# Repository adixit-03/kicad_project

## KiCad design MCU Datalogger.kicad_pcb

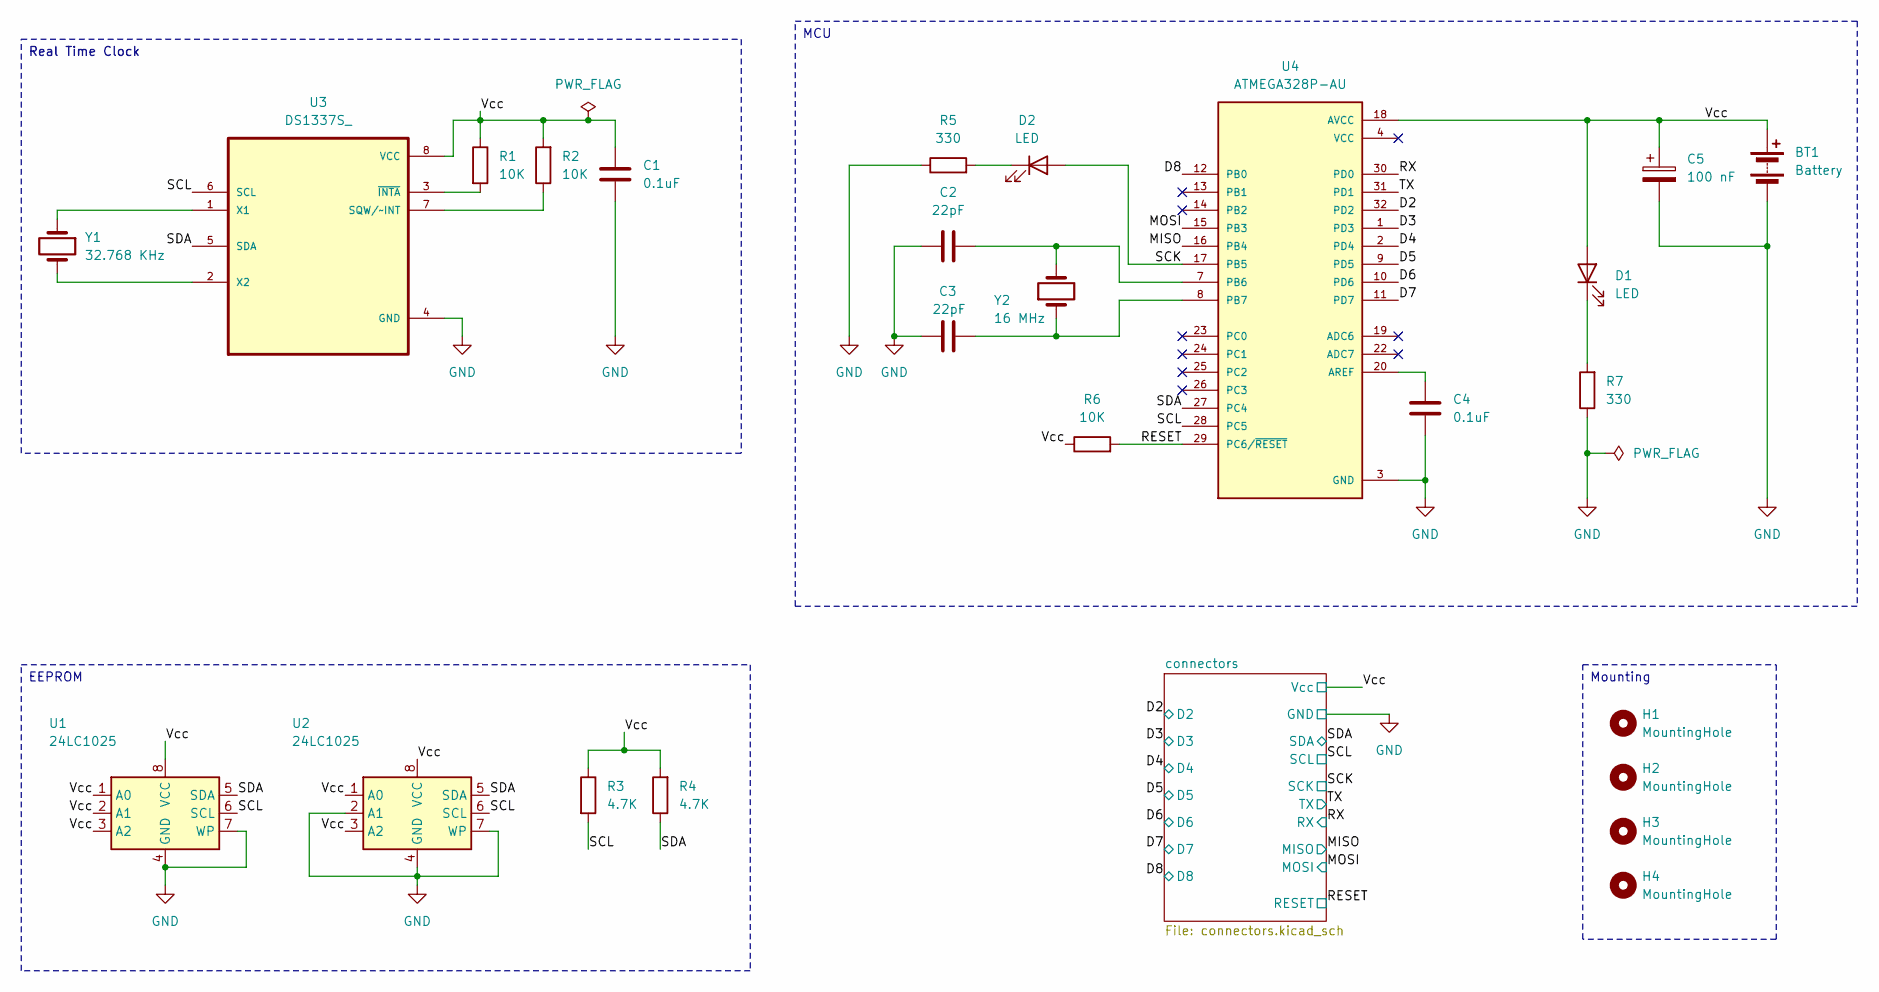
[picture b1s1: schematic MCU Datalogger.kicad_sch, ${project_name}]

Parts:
BT1: Battery; PinHeader_1x02_P2.54mm_Vertical
C1, C4: 0.1uF; C_0805_2012Metric
C2, C3: 22pF; C_0805_2012Metric
C5: 100 nF; C_0805_2012Metric
D1, D2: LED; LED_0805_2012Metric
H1, H2, H3, H4: MountingHole; MountingHole_2.1mm
R1, R2, R6: 10K; R_0805_2012Metric
R3, R4: 4.7K; R_0805_2012Metric
R5, R7: 330; R_0805_2012Metric
U1, U2: 24LC1025; SOIC-8_5.3x5.3mm_P1.27mm
U3: DS1337S_; SOIC127P600X175-8N
U4: ATMEGA328P-AU; QFP80P900X900X120-32N; PARTREV 8271A
Y1: 32.768 KHz; Crystal_SMD_5032-2Pin_5.0x3.2mm_HandSoldering
Y2: 16 MHz; Crystal_SMD_5032-2Pin_5.0x3.2mm_HandSoldering

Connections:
/D2: U4.32 (PD2); also elsewhere on the board
/D3: U4.1 (PD3); also elsewhere on the board
/D4: U4.2 (PD4); also elsewhere on the board
/D5: U4.9 (PD5); also elsewhere on the board
/D6: U4.10 (PD6); also elsewhere on the board
/D7: U4.11 (PD7); also elsewhere on the board
/D8: U4.12 (PB0); also elsewhere on the board
/MISO: U4.16 (PB4); also elsewhere on the board
/MOSI: U4.15 (PB3); also elsewhere on the board
/RESET: R6.2, U4.29 (PC6/~RESET); also elsewhere on the board
/RX: U4.30 (PD0); also elsewhere on the board
/SCK: D2.2 (A), U4.17 (PB5); also elsewhere on the board
/SCL: R3.2, U1.6 (SCL), U2.6 (SCL), U3.6 (SCL), U4.28 (PC5); also elsewhere on the board
/SDA: R4.1, U1.5 (SDA), U2.5 (SDA), U3.5 (SDA), U4.27 (PC4); also elsewhere on the board
/TX: U4.31 (PD1); also elsewhere on the board
/Vcc: BT1.1 (+), C1.2, C5.1, D1.2 (A), R1.1, R2.2, R3.1, R4.2, R6.1, U1.1 (A0), U1.2 (A1), U1.3 (A2), U1.8 (VCC), U2.1 (A0), U2.3 (A2), U2.8 (VCC), U3.8 (VCC), U4.18 (AVCC); also elsewhere on the board
GND: BT1.2 (-), C1.1, C2.1, C3.1, C4.1, C5.2, R5.1, R7.1, U1.4 (GND), U1.7 (WP), U2.2 (A1), U2.4 (GND), U2.7 (WP), U3.4 (GND), U4.3 (GND), U4.5 (GND), U4.21 (GND); also elsewhere on the board
unnamed: D1.1 (K), R7.2
unnamed: D2.1 (K), R5.2
unnamed: R2.1, U3.7 (SQW/~INT)
unnamed: U3.1 (X1), Y1.1
unnamed: U3.2 (X2), Y1.2
unnamed: R1.2, U3.3 (~INTA)
unnamed: C4.2, U4.20 (AREF)
unnamed: C2.2, U4.7 (PB6), Y2.2
unnamed: C3.2, U4.8 (PB7), Y2.1
VCC: U4.4 (VCC), U4.6 (VCC)

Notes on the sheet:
Mounting
Real Time Clock
MCU
EEPROM

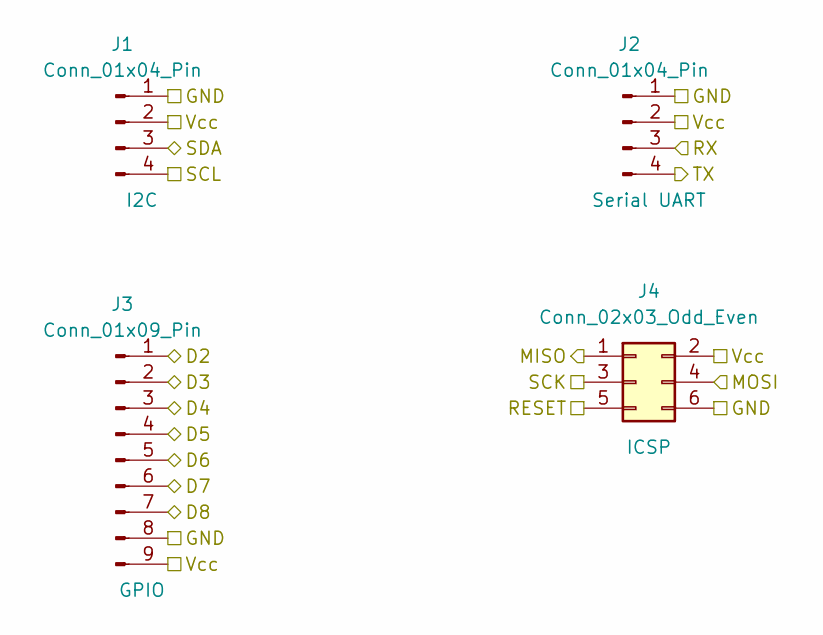
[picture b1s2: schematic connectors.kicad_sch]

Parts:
J1, J2: Conn_01x04_Pin; PinHeader_1x04_P2.54mm_Vertical
J3: Conn_01x09_Pin; PinHeader_1x09_P2.54mm_Vertical
J4: Conn_02x03_Odd_Even; PinHeader_2x03_P2.54mm_Vertical

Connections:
/D2: J3.1; also elsewhere on the board
/D3: J3.2; also elsewhere on the board
/D4: J3.3; also elsewhere on the board
/D5: J3.4; also elsewhere on the board
/D6: J3.5; also elsewhere on the board
/D7: J3.6; also elsewhere on the board
/D8: J3.7; also elsewhere on the board
/MISO: J4.1; also elsewhere on the board
/MOSI: J4.4; also elsewhere on the board
/RESET: J4.5; also elsewhere on the board
/RX: J2.3; also elsewhere on the board
/SCK: J4.3; also elsewhere on the board
/SCL: J1.4; also elsewhere on the board
/SDA: J1.3; also elsewhere on the board
/TX: J2.4; also elsewhere on the board
/Vcc: J1.2, J2.2, J3.9, J4.2; also elsewhere on the board
GND: J1.1, J2.1, J3.8, J4.6; also elsewhere on the board

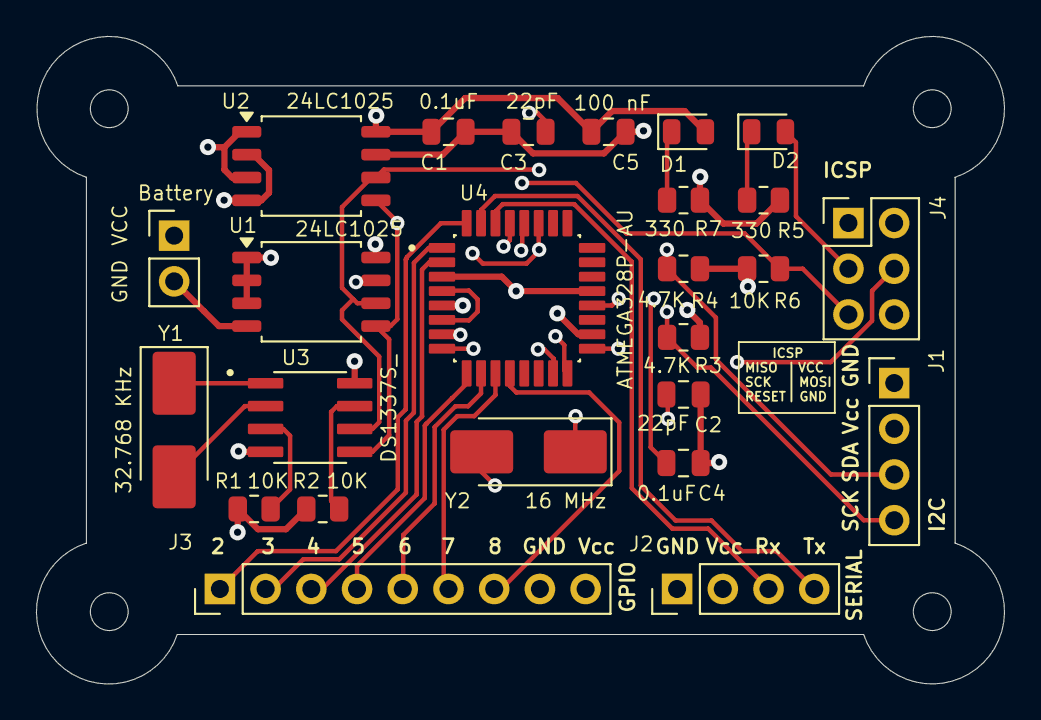
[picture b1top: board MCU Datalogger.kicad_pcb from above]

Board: 4 copper layers, 53.8 x 36.0 mm, 29 parts (0 on the bottom side), 27 nets.

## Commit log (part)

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2026-06-19 Setup of EEschema for new project.
2026-06-23 Have added required symbols to the schematic sheets.
2026-06-24 Changed locations of symbols (arrange).
2026-06-24 Added component values.
2026-06-24 Completed symbol-footprint associations.
2026-06-24 Completed wiring on main sheet.
2026-06-24 Completed wiring in the second sheet.
2026-06-26 Allocated GND and Vcc nets to power net class.
2026-06-26 Completed comments.
2026-06-26 Update MCU Datalogger project
2026-06-27 Setup Pcbnew.
2026-06-27 Completed placements of footprints.
2026-06-28 routing sans GND Vcc complete.
2026-06-28 Completed routing.
2026-06-28 Refined routing completed.
2026-06-28 Fixed outstanding issues.
2026-06-29 Fixed two defects in the schematic.
2026-06-29 Fixed the defects in 2layer.
2026-06-29 Completed 2layer.
2026-06-29 Completed 2layer layout.
2026-06-29 created gerbers for 2layer.
2026-06-29 added gerber directories to gitignore.
2026-06-30 completed 4 layer layout.
